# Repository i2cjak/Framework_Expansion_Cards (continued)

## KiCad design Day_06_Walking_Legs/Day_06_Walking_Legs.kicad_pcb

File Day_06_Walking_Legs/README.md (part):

# Day 06 — Walking Legs (Quadruped 2-DOF Expansion Card Set)

Four identical USB Type-C Expansion Cards plug flush into the four rear-set expansion bays (`Y = +36.0 mm` & `+76.6 mm`) of a Framework Laptop 13, anchoring a pair of reversible **12-gauge (`2.03 mm`) `5052-H32` aluminum Flank Stance-Extension Rails (`mech/leg_flank_bracket.step`)** that bolt across both bays per side and cantilever `93 mm` forward along/under the solid CNC aluminum bottom cover (`Y = -72.0 .. +94.0 mm`) to carry the front walking legs `81.0 mm` forward of the front ports (`Y = -45.0 mm` & `+67.0 mm`, `112.0 mm` balanced wheelbase) so the ~`1.3 kg` laptop stands walk-ready and executes static crawl and dynamic trot gaits.

---

## System Architecture & Engineering Calculations

### 1. Laptop Mass, Leg Kinematics & Torque Budget
- **Laptop + 4-Leg Mass:** $m_{\text{total}} \approx 1.30\text{ kg} + 4 \times 0.065\text{ kg} = 1.56\text{ kg}$ ($W = 15.3\text{ N}$).
- **Static & Dynamic Ground Reaction per Leg:**
  - Standing on 4 legs: $F_{z,\text{4-leg}} = 3.83\text{ N}$.
  - Static 3-leg crawl stance (worst-case CoM shift): $F_{z,\text{crawl}} \approx 6.2\text{ N}$.
  - Dynamic diagonal trot peak ($1.5\times$ impact factor across 2 diagonal legs): $F_{z,\text{trot}} \approx 11.5\text{ N}$.
- **Sagittal 2-DOF Linkage & Bellcrank Pushrod Geometry (`mech/`, `0 / 85` Full-ROM 3D Collisions Verified via `mech/simulate_walking_rom.py`):**
  - **Both MG90S metal-gear micro-servos** mount horizontally side-by-side (`X = ±9.00 mm, Z = +22.10 mm`) inside a high-arch MJF PA12 saddle (`mech/leg_servo_pod.step`, `17.6 mm` overhead crank headroom) with **both brass output splines pointing outboard (`-Y`)**, so all pivots act in the **`X–Z` sagittal walking plane** across 6 dedicated non-overlapping `Y` planes (`9.70 mm` tibia-to-rail clearance, `6.70 mm` pushrod-to-rail clearance, `3.17 mm` inboard-femur-to-pushrod clearance).
  - **Paired Upper Femur Links (`mech/leg_femur_link.step`, `qty: 8`):** $L_1 = 38.0\text{ mm}$ (`2.03 mm` `5052-H32` aluminum) driven directly by the Hip servo horn (`J2`) in symmetric double shear, supported outboard by `mech/leg_hip_bracket.step` (`ALU-063` overhead outrigger bridge) so radial ground loads bypass the servo shafts.
  - **Non-Crossing 4-Bar Knee Drive (`mech/leg_knee_pushrod.step`, `qty: 4` + `mech/leg_tibia_strut.step`, `qty: 4`):** The Knee servo (`J3`) drives a $12.0\text{ mm}$ crank arm coupled via a $36.0\text{ mm}$ `5052-H32` pushrod ($31.1^\circ\text{–}93.7^\circ$ transmission angle across the entire $48\times 26\text{ mm}$ foot workspace — zero dead-center singularity) to an integral $12.0\text{ mm}$ $90^\circ$ bellcrank lobe on the CNC-bent $61.5\text{ mm}$ ($L_2 = 47.0\text{ mm}$) sagittal U-channel tibia strut with an **open $15.0\text{ mm}$ upper clevis throat** (`Z = 39.5..61.5 mm`) so the twin femur links flex freely without front-web interference.
  - **Series-Elastic Compliant Arch Foot (`mech/leg_foot_pad.step`, `qty: 4`):** Printed in `95A` TPU (`22.5 mm` high-clearance ankle clevis tongue) with a through-arch oval suspension window flanked by twin elastomeric leaf-spring ribs ($\approx 3\text{ mm}$ progressive shock travel on foot strike) to cushion desk impacts and protect the servo gear trains.
  - Closed-loop 5-bar Jacobian virtual-work simulation (`m = 1.58 kg`):
    - 4-leg stand: $\tau_{\text{hip}} = 0.15\text{ N}\cdot\text{m}$ ($35\%$ of stall).
    - Static crawl peak joint torque: $\tau_{\text{crawl}} = \mathbf{0.30\text{ N}\cdot\text{m}}$ ($68\%$ of stall).
    - Paced diagonal trot ($0.85\text{ Hz}$): $\tau_{\text{trot}} = \mathbf{0.32\text{ N}\cdot\text{m}}$ ($73\%$ of the $\mathbf{0.44\text{ N}\cdot\text{m}}$ / $4.5\text{ kg}\cdot\text{cm}$ stall rating at $6.04\text{ V}$).

### 2. Framework Laptop 13 USB-C Port Power Validation (`2× 5 V @ 3.0 A` + `2× 5 V @ 1.5 A` = `45.0 W` PD Host Budget)
- **Host Port Specification:** With USB-PD wall power attached, two Framework Laptop 13 expansion bays source up to **`5.0 V @ 3.0 A` (`15.0 W` each = `30.0 W`)** and the other two bays source up to **`5.0 V @ 1.5 A` (`7.5 W` each = `15.0 W`)**, providing **`45.0 W` (`9.0 A @ 5.0 V`)** total across all four legs. Because two legs always land on **`1.5 A` (`7.5 W`)** bays, `1.50 A` on `5 V` `VBUS` is the binding per-leg design ceiling.
- **Simulated Per-Port & 4-Port `VBUS` Load (`mech/simulate_walking_rom.py`, `MT3608` `6.04 V` boost @ $\eta = 89\%$ + `32 mA` MCU/telemetry):**
  - **4-Leg Stand:** `0.57 A` avg / **`0.58 A` peak per port (`2.88 W`)** — `38.5%` of `1.5 A` port, `11.5 W` / `45.0 W` total.
  - **Belly Push-Up (`14 mm` stroke):** `0.48 A` avg / **`1.26 A` peak per port (`6.27 W`)** — `83.7%` of `1.5 A` port, `25.1 W` / `45.0 W` total.
  - **Static Crawl (`28 mm` stride):** `0.72 A` avg / **`1.22 A` peak per port (`6.08 W`)** — `81.0%` of `1.5 A` port, `16.3 W` / `45.0 W` total.
  - **Paced Diagonal Trot (`0.85 Hz`):** `0.67 A` avg / **`1.51 A` raw impact peak** (`17.7 W` / `45.0 W` 4-port total) — supplied locally during `~20 ms` foot-strike peaks by the `88 µF` (`+6V0_SERVO`) ceramic reservoir and capped below `1.50 A` at **`1.38 A`** on `1.5 A` ports.
  - **Sprint Trot (`1.05 Hz`) / Dual-Servo Hard Stall (`2.53 A` raw):** `3.0 A` (`15 W`) ports carry full dual-servo stall continuously (`84%`), whereas `1.5 A` (`7.5 W`) ports are protected by **`0.14 ms` hardware overcurrent foldback** (`INA226` `140 µs` `SOL` alert at **`1.38 A` / `27.6 mV`** across `R8` wired to `PB12` `EXTI12` ISR — $>30\times$ faster than the motherboard port switch OCP!).
- **Pulsed `12 ms` Precharge Soft-Start (`0.22 A` Peak vs `32.4 A` Hard Step):**
  1. Snapping `Q1` (`AO3401A`) hard ON into `110 µF` total capacitance (`C12 = 22 µF` + `4× 22 µF = 88 µF` boost reservoir through `L1`/`D4`) would draw a `32.4 A` microsecond spike and trip a `1.5 A` port switch.
  2. `firmware/main.c` (`set_servo_power`) staggers each bay by `bay_id × 40 ms` and pulses `PB4` at `25 kHz` (`1 → 8 µs` duty over `12 ms`) while `BOOST_EN = LOW`, using `L1`'s `di/dt` limit to precharge the `110 µF` bank to `4.70 V` at **`0.22 A` peak port current** before latching `Q1` ON and enabling `U5` (`MT3608` `6.04 V`).

### 3. Sub-Microsecond Multi-Card Gait Coordination (`1 kHz` USB `SOF`)
- All four Expansion Cards enumerate on the laptop's internal xHCI root hub, which broadcasts the USB Full-Speed **Start-Of-Frame (`SOF`)** packet every `1.000 ms` with `< 500 ns` skew across all four ports.
- `software/walk_controller.py` streams trajectory packets tagged with a target 11-bit `SOF` frame number `(FNR + 5) & 0x7FF`.
- On each card, `USB_LP_CAN1_RX0_IRQHandler` phase-locks `TIM2`'s `200 Hz` (`5000 µs`, `1 µs` resolution) hardware PWM counter to `FNR % 5 == 0` and commits `HIP_PWM` (`PA0`) and `KNEE_PWM` (`PA1`) simultaneously on the target `SOF` edge—achieving deterministic 4-leg synchronization with zero external sync wires.

### 4. Rear-Set Port Geometry, Reversible `ALU-080` Flank Stance-Extension Rail & SendCutSend DFM
- **Why Direct Port Mounting Fails Fore-Aft Balance (`FW_MAIN_PCB_GENERIC_2` Port Coordinates):** On a Framework Laptop 13 (`228.9 mm` front-to-back, `Y = -114.45 .. +114.45 mm`), **both** physical Expansion Card bays on each flank sit in the **rear half** of the laptop (`Y = +36.0 mm` Front Port and `Y = +76.6 mm` Rear Port, `40.60 mm` center-to-center pitch with a `10.6 mm` aluminum divider), while the entire front `135.45 mm` (`Y = -114.45 .. +21.0 mm`, battery + palmrest) has zero expansion bays. Mounting legs directly at the ports would leave `150 mm` of unsupported front laptop mass ahead of the front legs.
- **Reversible Flank Stance-Extension Rail (`mech/leg_flank_bracket.step`, `ALU-080` `2.03 mm` `12-gauge` `5052-H32`, `qty: 2`):** Each `166.0 × 49.0 × 12.5 mm` CNC-bent inverted U-channel rail (`Y = -24.5 .. +24.5 mm`, giving `9.70 mm` outboard clearance to the `leg_tibia_strut` U-channel and `6.70 mm` clearance to `leg_knee_pushrod`) bolts across **both** rear-set `leg_bay_housing` plugs on a flank (`8× M2.5` across the `40.6 mm` two-bay baseline, locking out yaw twist) and extends **`93 mm` forward** along the laptop flank and `24.5 mm` underneath the solid CNC aluminum bottom cover (`Y = -72.0 .. +94.0 mm`, clearing both the `|X| = 111.5 mm` card-release latch buttons and the `Y = ±103 mm` rubber foot strips). It carries the **Front `leg_servo_pod` at `Y = -45.0 mm`** (`81.0 mm` forward of the Front Port — reacting front-leg vertical loads straight upward into the solid aluminum bottom cover right above `Y = -45.0 mm` with zero port prying!) and the **Rear `leg_servo_pod` at `Y = +67.0 mm`** (`112.0 mm` balanced quadruped wheelbase). A mirror-symmetric 24-hole layout lets **one single reversible SKU (`qty: 2`)** fit both Left and Right flanks (`37 pass · 0 fail · 0 warn` SendCutSend live DFM).
- **Modular Printed Plugs & Saddles (`MJF PA12 Nylon`):**
  - `mech/leg_bay_housing.step` (`qty: 4`) — Open-top `30 × 32 × 6.8 mm` Expansion Card bay cartridge housing the double-sided `5.44 mm` Z-span `Day_06` PCB (`SM03B-SRSS-TB(LF)(SN)` `1.0 mm` JST-SH side-entry servo headers `J2`/`J3`, `MWSA0518S-4R7MT` `1.8 mm` shielded inductor `L1`, and `SS34FA` `SOD-123F` Schottky `D4` — verified `0.000 mm³` interference across all 86 3D component solids) at `Y = +36.0` & `+76.6 mm`, with straight-in front mating for dual 3-wire `#28 AWG` silicone servo harnesses (`4× M2.5 × 2.5 mm` floor heat-set inserts).
  - `mech/leg_servo_pod.step` (`qty: 4`) — Modular outboard dual-`MG90S` saddle (`27.50 mm` exact servo ear pitch) bolted at `Y = -45.0` & `+67.0 mm` on the outboard deck of `leg_flank_bracket` (`4× M2.5 × 3.0 mm` floor heat-set inserts + `4× M2.5 × 3.0 mm` roof heat-set inserts for `leg_hip_bracket`).
- **SendCutSend `5052-H32` Aluminum Sheet-Metal Set (`0 fail · 0 warn` live DFM verified across all 5 sheet-metal parts):**
  - `mech/leg_flank_bracket.flat.dxf` (`ALU-080` `2.03 mm` CNC-bent `166.0 mm` reversible flank stance-extension U-channel rail, `qty: 2` — `37 pass · 0 fail · 0 warn`).
  - `mech/leg_hip_bracket.flat.dxf` (`ALU-063` `1.60 mm` CNC-bent 90° overhead double-shear bearing outrigger, `qty: 4` — `25 pass · 0 fail · 0 warn`).
  - `mech/leg_femur_link.dxf` (`ALU-080` `2.03 mm` laser-cut `38.0 mm` sagittal femur link, `qty: 8` — `13 pass · 0 fail · 0 warn`).
  - `mech/leg_knee_pushrod.dxf` (`ALU-080` `2.03 mm` laser-cut `36.0 mm` knee actuation pushrod, `qty: 4` — `13 pass · 0 fail · 0 warn`).
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
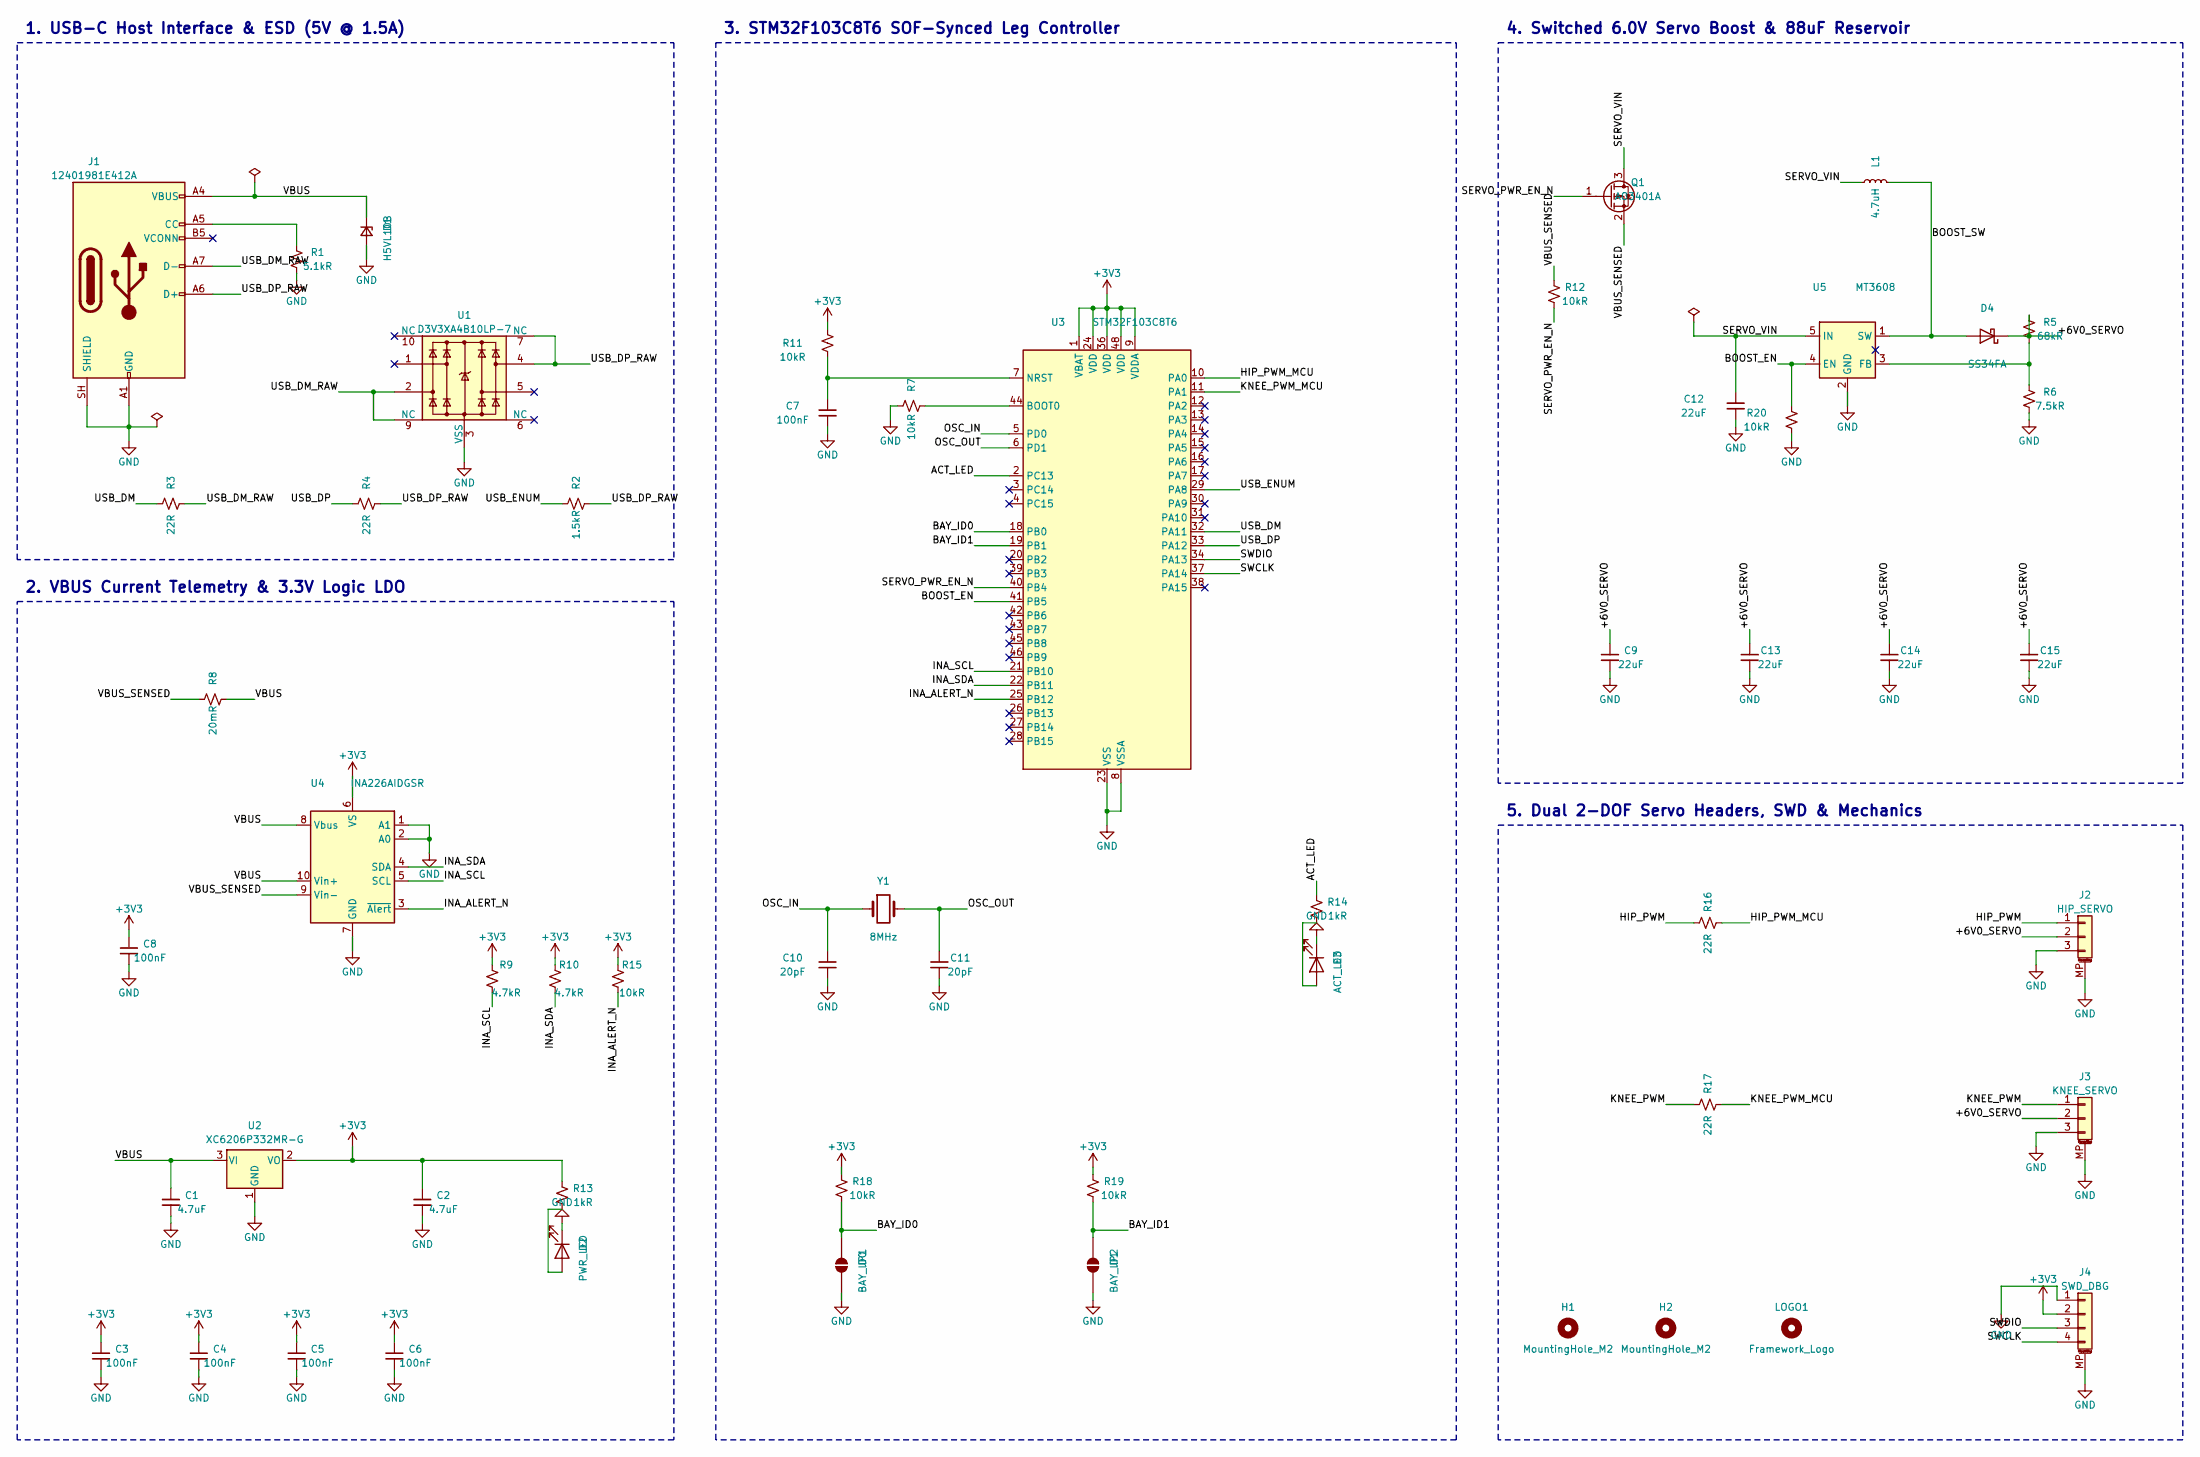
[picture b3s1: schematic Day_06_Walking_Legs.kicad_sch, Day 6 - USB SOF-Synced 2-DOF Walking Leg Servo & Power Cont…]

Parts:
C1, C2: 4.7uF; C_0603_1608Metric; MPN CL10A475KO8NNNC; LCSC C19666
C3, C4, C5, C6, C7, C8: 100nF; C_0402_1005Metric; MPN CL05B104KB54PNC; LCSC C307331
C9, C12, C13, C14, C15: 22uF; C_1206_3216Metric; MPN CL31A226KAHNNNE; LCSC C12891
C10, C11: 20pF; C_0402_1005Metric; MPN 0402CG200J500NT; LCSC C1554
D1: H5VL10B; D_SOD-882; MPN H5VL10B; LCSC C7420372
D2: PWR_LED; LED_0603_1608Metric; MPN KT-0603W; LCSC C2290
D3: ACT_LED; LED_0603_1608Metric; MPN KT-0603R; LCSC C2286
D4: SS34FA; D_SOD-123F; MPN SS34FA; LCSC C719833
H1, H2: MountingHole_M2; MountingHole_2.2mm_M2
J1: 12401981E412A; USB_C_Plug_Amphenol_12401981E412A; MPN 12401981E412A; LCSC C5428559
J2: HIP_SERVO; JST_SH_SM03B-SRSS-TB_1x03-1MP_P1.00mm_Horizontal; MPN SM03B-SRSS-TB(LF)(SN); LCSC C160403
J3: KNEE_SERVO; JST_SH_SM03B-SRSS-TB_1x03-1MP_P1.00mm_Horizontal; MPN SM03B-SRSS-TB(LF)(SN); LCSC C160403
J4: SWD_DBG; JST_SH_SM04B-SRSS-TB_1x04-1MP_P1.00mm_Horizontal; MPN SM04B-SRSS-TB(LF)(SN); LCSC C160404
JP1: BAY_ID0; SolderJumper-2_P1.3mm_Open_RoundedPad1.0x1.5mm
JP2: BAY_ID1; SolderJumper-2_P1.3mm_Open_RoundedPad1.0x1.5mm
L1: 4.7uH; L_Sunlord_MWSA0518S; MPN MWSA0518S-4R7MT; LCSC C408347
LOGO1: Framework_Logo; Framework-Logo_1.5mm_SilkScreen
Q1: AO3401A; SOT-23; MPN AO3401A; LCSC C15127
R1: 5.1kR; R_0402_1005Metric; MPN 0402WGF5101TCE; LCSC C25905
R2: 1.5kR; R_0402_1005Metric; MPN 0402WGF1501TCE; LCSC C25867
R3, R4, R16, R17: 22R; R_0402_1005Metric; MPN 0402WGF220JTCE; LCSC C25092
R5: 68kR; R_0402_1005Metric; MPN 0402WGF6802TCE; LCSC C36871
R6: 7.5kR; R_0402_1005Metric; MPN 0402WGF7501TCE; LCSC C25918
R7, R11, R12, R15, R18, R19, R20: 10kR; R_0402_1005Metric; MPN 0402WGF1002TCE; LCSC C25744
R8: 20mR; R_1206_3216Metric; MPN 1206W3F200MT5E; LCSC C2765435
R9, R10: 4.7kR; R_0402_1005Metric; MPN 0402WGF4701TCE; LCSC C25900
R13, R14: 1kR; R_0402_1005Metric; MPN 0402WGF1001TCE; LCSC C11702
U1: D3V3XA4B10LP-7; Diodes_UDFN-10_1x2.5mm_P0.5mm; MPN D3V3XA4B10LP-7; LCSC C1980462
U2: XC6206P332MR-G; SOT-23; MPN XC6206P332MR-G; LCSC C5446
U3: STM32F103C8T6; LQFP-48_7x7mm_P0.5mm; MPN STM32F103C8T6; LCSC C8734
U4: INA226AIDGSR; MSOP-10_3x3mm_P0.5mm; MPN INA226AIDGSR; LCSC C49851
U5: MT3608; SOT-23-6; MPN MT3608; LCSC C84817
Y1: 8MHz; Crystal_SMD_5032-2Pin_5.0x3.2mm; MPN X50328MSB2GI; LCSC C115962

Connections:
+3V3: C2.1, C3.1, C4.1, C5.1, C6.1, C8.1, J4.2, R9.1, R10.1, R11.1, R13.1, R15.1, R18.1, R19.1, U2.2 (VO), U3.1 (VBAT), U3.9 (VDDA), U3.24 (VDD), U3.36 (VDD), U3.48 (VDD), U4.6 (VS)
/+6V0_SERVO: C9.1, C13.1, C14.1, C15.1, D4.1 (K), J2.2, J3.2, R5.1
/ACT_LED: R14.1, U3.2 (PC13)
/BAY_ID0: JP1.2 (B), R18.2, U3.18 (PB0)
/BAY_ID1: JP2.2 (B), R19.2, U3.19 (PB1)
/BOOST_EN: R20.1, U3.41 (PB5), U5.4 (EN)
/BOOST_SW: D4.2 (A), L1.2, U5.1 (SW)
/HIP_PWM: J2.1, R16.1
/HIP_PWM_MCU: R16.2, U3.10 (PA0)
/INA_ALERT_N: R15.2, U3.25 (PB12), U4.3 (~Alert)
/INA_SCL: R9.2, U3.21 (PB10), U4.5 (SCL)
/INA_SDA: R10.2, U3.22 (PB11), U4.4 (SDA)
/KNEE_PWM: J3.1, R17.1
/KNEE_PWM_MCU: R17.2, U3.11 (PA1)
/OSC_IN: C10.1, U3.5 (PD0), Y1.1
/OSC_OUT: C11.1, U3.6 (PD1), Y1.2
/SERVO_PWR_EN_N: Q1.1 (G), R12.2, U3.40 (PB4)
/SERVO_VIN: C12.1, L1.1, Q1.3 (D), U5.5 (IN)
/SWCLK: J4.4, U3.37 (PA14)
/SWDIO: J4.3, U3.34 (PA13)
/USB_DM: R3.1, U3.32 (PA11)
/USB_DM_RAW: J1.A7 (D-), R3.2, U1.2, U1.9 (NC)
/USB_DP: R4.1, U3.33 (PA12)
/USB_DP_RAW: J1.A6 (D+), R2.2, R4.2, U1.4, U1.7 (NC)
/USB_ENUM: R2.1, U3.29 (PA8)
/VBUS: C1.1, D1.1 (K), J1.A4 (VBUS), J1.A9 (VBUS), J1.B4 (VBUS), J1.B9 (VBUS), R8.2, U2.3 (VI), U4.8 (Vbus), U4.10 (Vin+)
/VBUS_SENSED: Q1.2 (S), R8.1, R12.1, U4.9 (Vin-)
GND: C1.2, C2.2, C3.2, C4.2, C5.2, C6.2, C7.2, C8.2, C9.2, C10.2, C11.2, C12.2, C13.2, C14.2, C15.2, D1.2 (A), D2.1 (K), D3.1 (K), J1.A1 (GND), J1.A12 (GND), J1.B1 (GND), J1.B12 (GND), J1.SH (SHIELD), J2.3, J2.MP (MountPin), J3.3, J3.MP (MountPin), J4.1, J4.MP (MountPin), JP1.1 (A), JP2.1 (A), R1.2, R6.2, R7.1, R20.2, U1.3 (VSS), U1.8 (VSS), U2.1 (GND), U3.8 (VSSA), U3.23 (VSS), U3.35 (VSS), U3.47 (VSS), U4.1 (A1), U4.2 (A0), U4.7 (GND), U5.2 (GND)
unnamed: D2.2 (A), R13.2
unnamed: D3.2 (A), R14.2
unnamed: J1.A5 (CC), R1.1
unnamed: R7.2, U3.44 (BOOT0)
unnamed: C7.1, R11.2, U3.7 (NRST)
unnamed: R5.2, R6.1, U5.3 (FB)

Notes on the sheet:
1. USB-C Host Interface & ESD (5V @ 1.5A)
2. VBUS Current Telemetry & 3.3V Logic LDO
3. STM32F103C8T6 SOF-Synced Leg Controller
4. Switched 6.0V Servo Boost & 88uF Reservoir
5. Dual 2-DOF Servo Headers, SWD & Mechanics

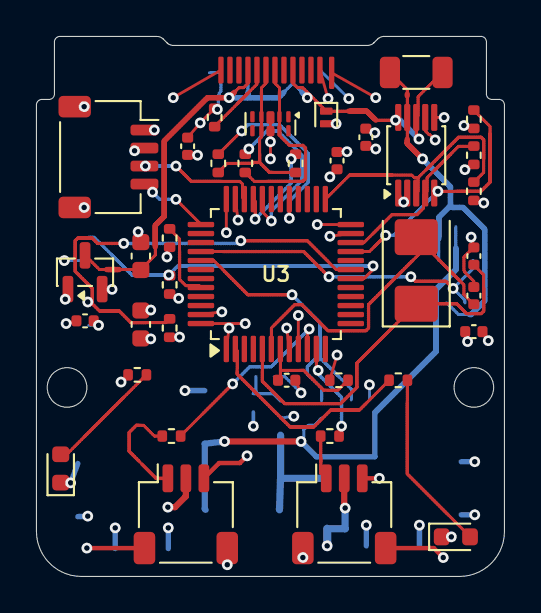
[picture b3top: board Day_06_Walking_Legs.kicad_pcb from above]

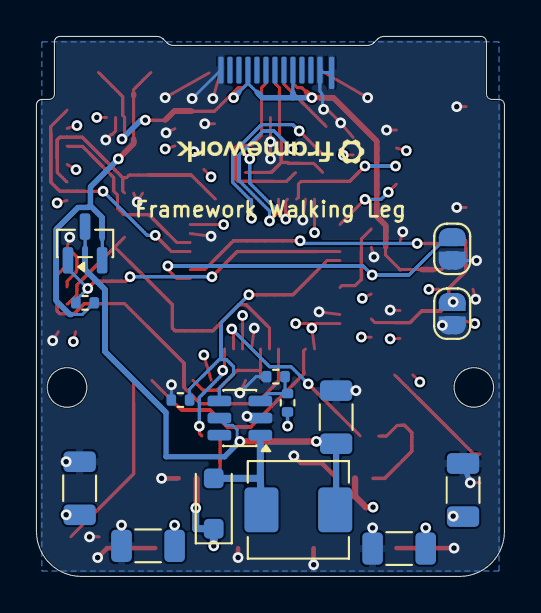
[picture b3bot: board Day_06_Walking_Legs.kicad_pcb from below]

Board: 4 copper layers, 26.0 x 30.0 mm, 56 parts (16 on the bottom side), 34 nets.

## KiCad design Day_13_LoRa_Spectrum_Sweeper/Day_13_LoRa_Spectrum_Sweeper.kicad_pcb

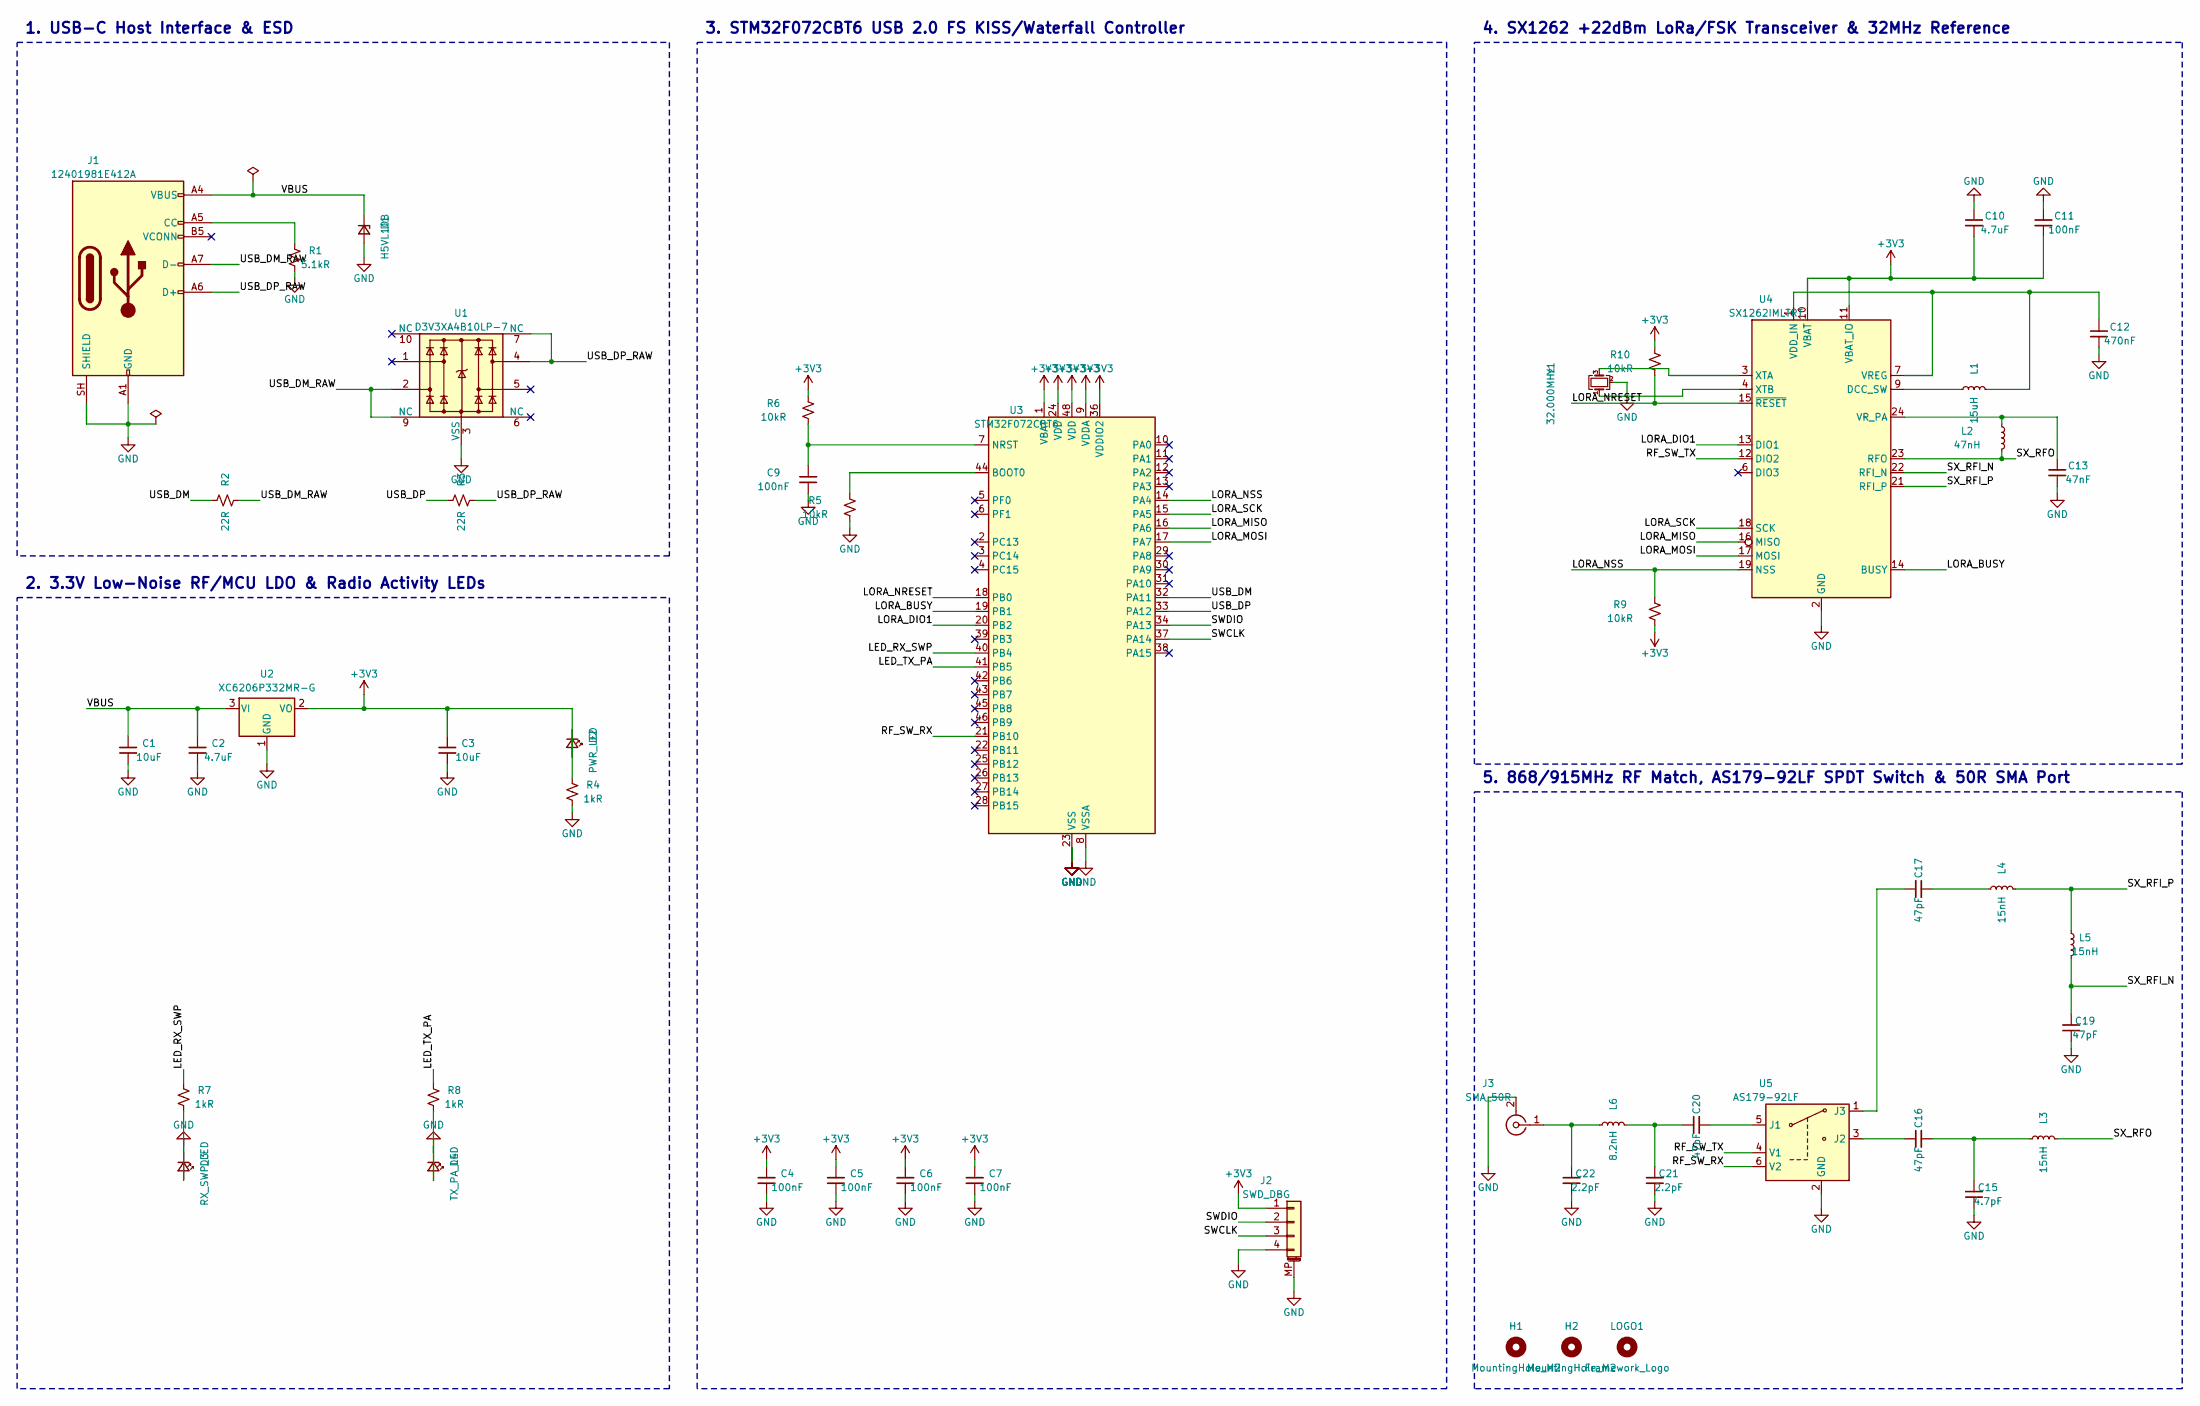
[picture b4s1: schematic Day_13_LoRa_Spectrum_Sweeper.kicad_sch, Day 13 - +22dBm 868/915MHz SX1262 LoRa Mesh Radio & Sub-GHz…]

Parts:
C1, C3: 10uF; C_0805_2012Metric; MPN CL21A106KAYNNNE; LCSC C15850
C2, C10: 4.7uF; C_0603_1608Metric; MPN CL10A475KO8NNNC; LCSC C19666
C4, C5, C6, C7, C9, C11: 100nF; C_0402_1005Metric; MPN CL05B104KB54PNC; LCSC C307331
C12: 470nF; C_0402_1005Metric; MPN CL05A474KP5NNNC; LCSC C47339
C13: 47nF; C_0402_1005Metric; MPN TCC0402X7R473K500AT; LCSC C880605
C15: 4.7pF; C_0402_1005Metric; MPN 0402CG4R7C500NT; LCSC C1569
C16, C17, C19, C20: 47pF; C_0402_1005Metric; MPN 0402CG470J500NT; LCSC C1567
C21, C22: 2.2pF; C_0402_1005Metric; MPN 0402CG2R2C500NT; LCSC C1559
D1: H5VL10B; D_SOD-882; MPN H5VL10B; LCSC C7420372
D2: PWR_LED; LED_0603_1608Metric; MPN 19-217/GHC-YR1S2/3T; LCSC C2290
D3: RX_SWP_LED; LED_0603_1608Metric; MPN 19-217/GHC-YR1S2/3T; LCSC C2290
D4: TX_PA_LED; LED_0603_1608Metric; MPN KT-0603R; LCSC C2286
H1, H2: MountingHole_M2; MountingHole_2.2mm_M2
J1: 12401981E412A; USB_C_Plug_Amphenol_12401981E412A; MPN 12401981E412A; LCSC C5428559
J2: SWD_DBG; JST_SH_SM04B-SRSS-TB_1x04-1MP_P1.00mm_Horizontal; MPN SM04B-SRSS-TB(LF)(SN); LCSC C160404
J3: SMA_50R; SMA_Samtec_SMA-J-P-H-ST-EM1_EdgeMount; MPN BWSMA-KE-Z001; LCSC C496549
L1: 15uH; L_0603_1608Metric; MPN MGFL1608F150MT-LF; LCSC C486329
L2: 47nH; L_0402_1005Metric; MPN VHF100505HQ47NJT; LCSC C395068
L3, L4, L5: 15nH; L_0402_1005Metric; MPN SDCL1005C15NJTDF; LCSC C27143
L6: 8.2nH; L_0402_1005Metric; MPN LQG15HS8N2J02D; LCSC C98003
LOGO1: Framework_Logo; Framework-Logo_1.5mm_SilkScreen
R1: 5.1kR; R_0402_1005Metric; MPN 0402WGF5101TCE; LCSC C25905
R2, R3: 22R; R_0402_1005Metric; MPN 0402WGF220JTCE; LCSC C25092
R4, R7, R8: 1kR; R_0402_1005Metric; MPN 0402WGF1001TCE; LCSC C11702
R5, R6, R9, R10: 10kR; R_0402_1005Metric; MPN 0402WGF1002TCE; LCSC C25744
U1: D3V3XA4B10LP-7; Diodes_UDFN-10_1x2.5mm_P0.5mm; MPN D3V3XA4B10LP-7; LCSC C1980462
U2: XC6206P332MR-G; SOT-23; MPN XC6206P332MR-G; LCSC C5446
U3: STM32F072CBT6; LQFP-48_7x7mm_P0.5mm; MPN STM32F072CBT6; LCSC C81720
U4: SX1262IMLTRT; QFN-24-1EP_4x4mm_P0.5mm_EP2.5x2.5mm; MPN SX1262IMLTRT; LCSC C191341
U5: AS179-92LF; SOT-363_SC-70-6; MPN AS179-92LF; LCSC C83422
Y1: 32.000MHz; Crystal_SMD_3225-4Pin_3.2x2.5mm; MPN X322532MOB4SI; LCSC C9009

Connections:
+3V3: C3.1, C4.1, C5.1, C6.1, C7.1, C10.2, C11.2, D2.2 (A), J2.1, R6.1, R9.2, R10.1, U2.2 (VO), U3.1 (VBAT), U3.9 (VDDA), U3.24 (VDD), U3.36 (VDDIO2), U3.48 (VDD), U4.10 (VBAT), U4.11 (VBAT_IO)
/LED_RX_SWP: R7.1, U3.40 (PB4)
/LED_TX_PA: R8.1, U3.41 (PB5)
/LORA_BUSY: U3.19 (PB1), U4.14 (BUSY)
/LORA_DIO1: U3.20 (PB2), U4.13 (DIO1)
/LORA_MISO: U3.16 (PA6), U4.16 (MISO)
/LORA_MOSI: U3.17 (PA7), U4.17 (MOSI)
/LORA_NRESET: R10.2, U3.18 (PB0), U4.15 (~RESET)
/LORA_NSS: R9.1, U3.14 (PA4), U4.19 (NSS)
/LORA_SCK: U3.15 (PA5), U4.18 (SCK)
/RF_SW_RX: U3.21 (PB10), U5.6 (V2)
/RF_SW_TX: U4.12 (DIO2), U5.4 (V1)
/SWCLK: J2.3, U3.37 (PA14)
/SWDIO: J2.2, U3.34 (PA13)
/SX_RFI_N: C19.1, L5.2, U4.22 (RFI_N)
/SX_RFI_P: L4.2, L5.1, U4.21 (RFI_P)
/SX_RFO: L2.2, L3.2, U4.23 (RFO)
/USB_DM: R2.1, U3.32 (PA11)
/USB_DM_RAW: J1.A7 (D-), R2.2, U1.2, U1.9 (NC)
/USB_DP: R3.1, U3.33 (PA12)
/USB_DP_RAW: J1.A6 (D+), R3.2, U1.4, U1.7 (NC)
/VBUS: C1.1, C2.1, D1.1 (K), J1.A4 (VBUS), J1.A9 (VBUS), J1.B4 (VBUS), J1.B9 (VBUS), U2.3 (VI)
unnamed: C15.1, C16.2, L3.1
unnamed: C17.2, L4.1
unnamed: C20.1, C21.1, L6.2
unnamed: D2.1 (K), R4.1
unnamed: J1.A5 (CC), R1.1
unnamed: C22.1, J3.1 (In), L6.1
unnamed: R5.1, U3.44 (BOOT0)
unnamed: C9.1, R6.2, U3.7 (NRST)
unnamed: L1.1, U4.9 (DCC_SW)
unnamed: C12.1, L1.2, U4.1 (VDD_IN), U4.7 (VREG)
unnamed: C13.1, L2.1, U4.24 (VR_PA)
unnamed: U4.3 (XTA), Y1.3
unnamed: C20.2, U5.5 (J1)
unnamed: C16.1, U5.3 (J2)
unnamed: C17.1, U5.1 (J3)

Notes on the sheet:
1. USB-C Host Interface & ESD
2. 3.3V Low-Noise RF/MCU LDO & Radio Activity LEDs
3. STM32F072CBT6 USB 2.0 FS KISS/Waterfall Controller
4. SX1262 +22dBm LoRa/FSK Transceiver & 32MHz Reference
5. 868/915MHz RF Match, AS179-92LF SPDT Switch & 50R SMA Port

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
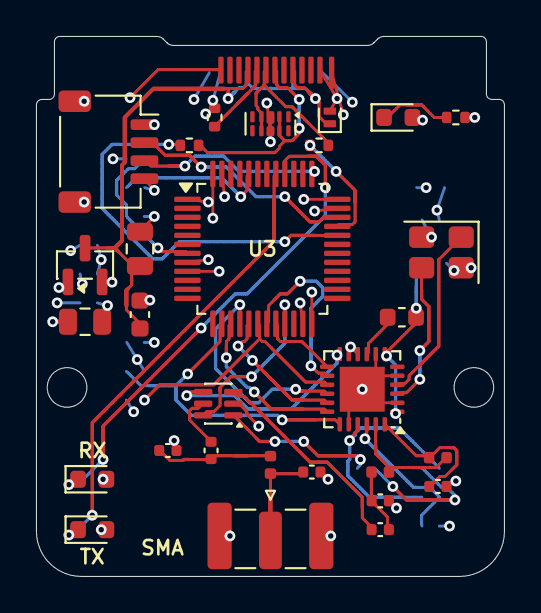
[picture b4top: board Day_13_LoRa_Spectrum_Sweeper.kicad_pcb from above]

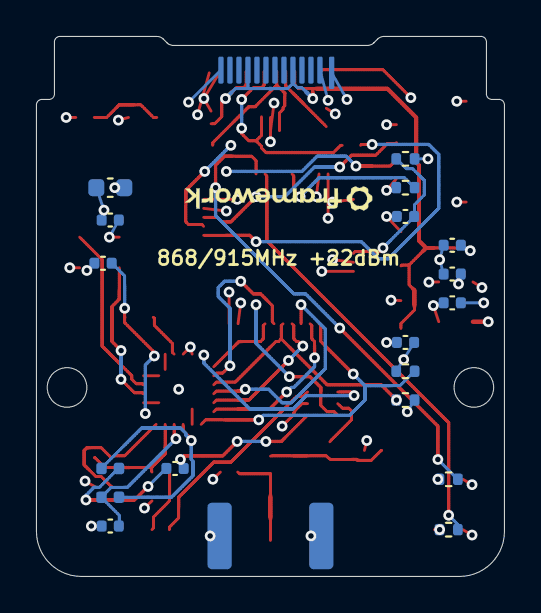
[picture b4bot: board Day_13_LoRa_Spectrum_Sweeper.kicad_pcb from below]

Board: 4 copper layers, 26.0 x 30.0 mm, 51 parts (19 on the bottom side), 41 nets.

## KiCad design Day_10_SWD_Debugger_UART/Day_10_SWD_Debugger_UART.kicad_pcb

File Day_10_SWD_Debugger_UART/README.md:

# Day 10 — Autoleveling `1.65V–5.5V` CMSIS-DAPv2 SWD Debugger & Target UART Bridge

A flush-fit ARM Cortex-M / RISC-V `CMSIS-DAPv2` hardware debug probe and `6 Mbps` target `UART` / `SWO` bridge inside a `26.0 × 30.0 mm` Framework Laptop Expansion Card, featuring true `1.65 V – 5.5 V` dual-supply level translation across every target signal.

## Hardware Architecture

1. **Five-Channel `420 Mbps` `1.65V–5.5V` Autoleveling Front-End (`U4`–`U8` — `5×` TI `SN74LVC1T45DBVR`):**
   - Each signal uses an independent dual-supply (`VCCA = +3.3 V`, `VCCB = VTREF`) `SOT-23-6` bus transceiver with `I_off` partial-power-down isolation: when a target board is powered off (`VTREF = 0 V`), all target pins remain high-impedance (`Hi-Z`) with zero back-powering.
   - **`U4` (`SWDIO`):** Hardware direction-controlled turnaround (`PB12` with `10 kΩ` reset pull-down `R17` so `U4` powers up in passive `B → A` input mode).
   - **`U5` (`SWCLK`):** Dedicated low-skew `SPI2_SCK` / GPIO clock translator (`PB13`).
   - **`U6` (`nRESET` Bidirectional Open-Drain + Target Reset Sense):** `PB0` controls `DIR` (`10 kΩ` pull-down `R18` defaults `U6` to `B → A` `Hi-Z` release at boot so `PB1` monitors external target reset button presses without contention; asserting `PB1 = 0` + `PB0 = 1` actively sinks target `nRESET` to `0.0 V` at `1.65 V – 5.5 V`).
   - **`U7` & `U8` (`UART TX` & `UART RX / SWO`):** Independent `USART2` DMA transmit/receive channels (`PA2`/`PA3`) with `22 Ω` series damping resistors (`R12`–`R16`) and weak `100 kΩ` RX idle pull-up (`R19`).

2. **`VTref` Surge Protection & Millivolt ADC Telemetry (`D3`, `R5`–`R7`, `C7`, `C8`):**
   - `H5VL10B` bidirectional TVS (`D3`), `22 Ω` surge limiter (`R5`), and `4.7 µF` + `5× 100 nF` decoupling condition the sensed target supply rail, while a `2:1` (`100 kΩ / 100 kΩ`) precision divider reports `0.00 V – 6.60 V` `VTref` to `PA0` (`ADC_IN0`) for `CMSIS-DAPv2` `DAP_Info` target-power verification.

3. **Crystal-Less USB 2.0 FS Controller & Dual Shrouded `1.0 mm` Bezel Ports (`U3`, `J2`, `J3`):**
   - `STM32F072CBT6` (`U3`, `48 MHz` `HSI48` + `CRS` `SOF` clock recovery) exposes `WinUSB` `CMSIS-DAPv2` bulk endpoints (zero-driver plug-and-play in `OpenOCD`, `pyOCD`, `probe-rs`, and `VS Code Cortex-Debug`) alongside a standard `CDC-ACM` Virtual COM Port.
   - Two side-by-side shrouded `4`-pin `1.0 mm` JST-SH connectors on the outward bezel separate `TGT_SWD` (`J2`: `VTref`, `SWDIO`, `SWCLK`, `GND`) and `TGT_UART` (`J3`: `nRESET`, `TGT_TX`, `TGT_RX`, `GND`) alongside `DAP` and `UART` activity LEDs (`D4`, `D5`).

## Fabrication & Build

All components are sourced from the fab's stock on a `0.8 mm` 4-layer ENIG stackup (`Day_10_SWD_Debugger_UART.fab.json`). Regenerate ERC/DRC reports, Gerbers, placement files, STEP model, and 3D renders with:

```bash
python3 build.py
```

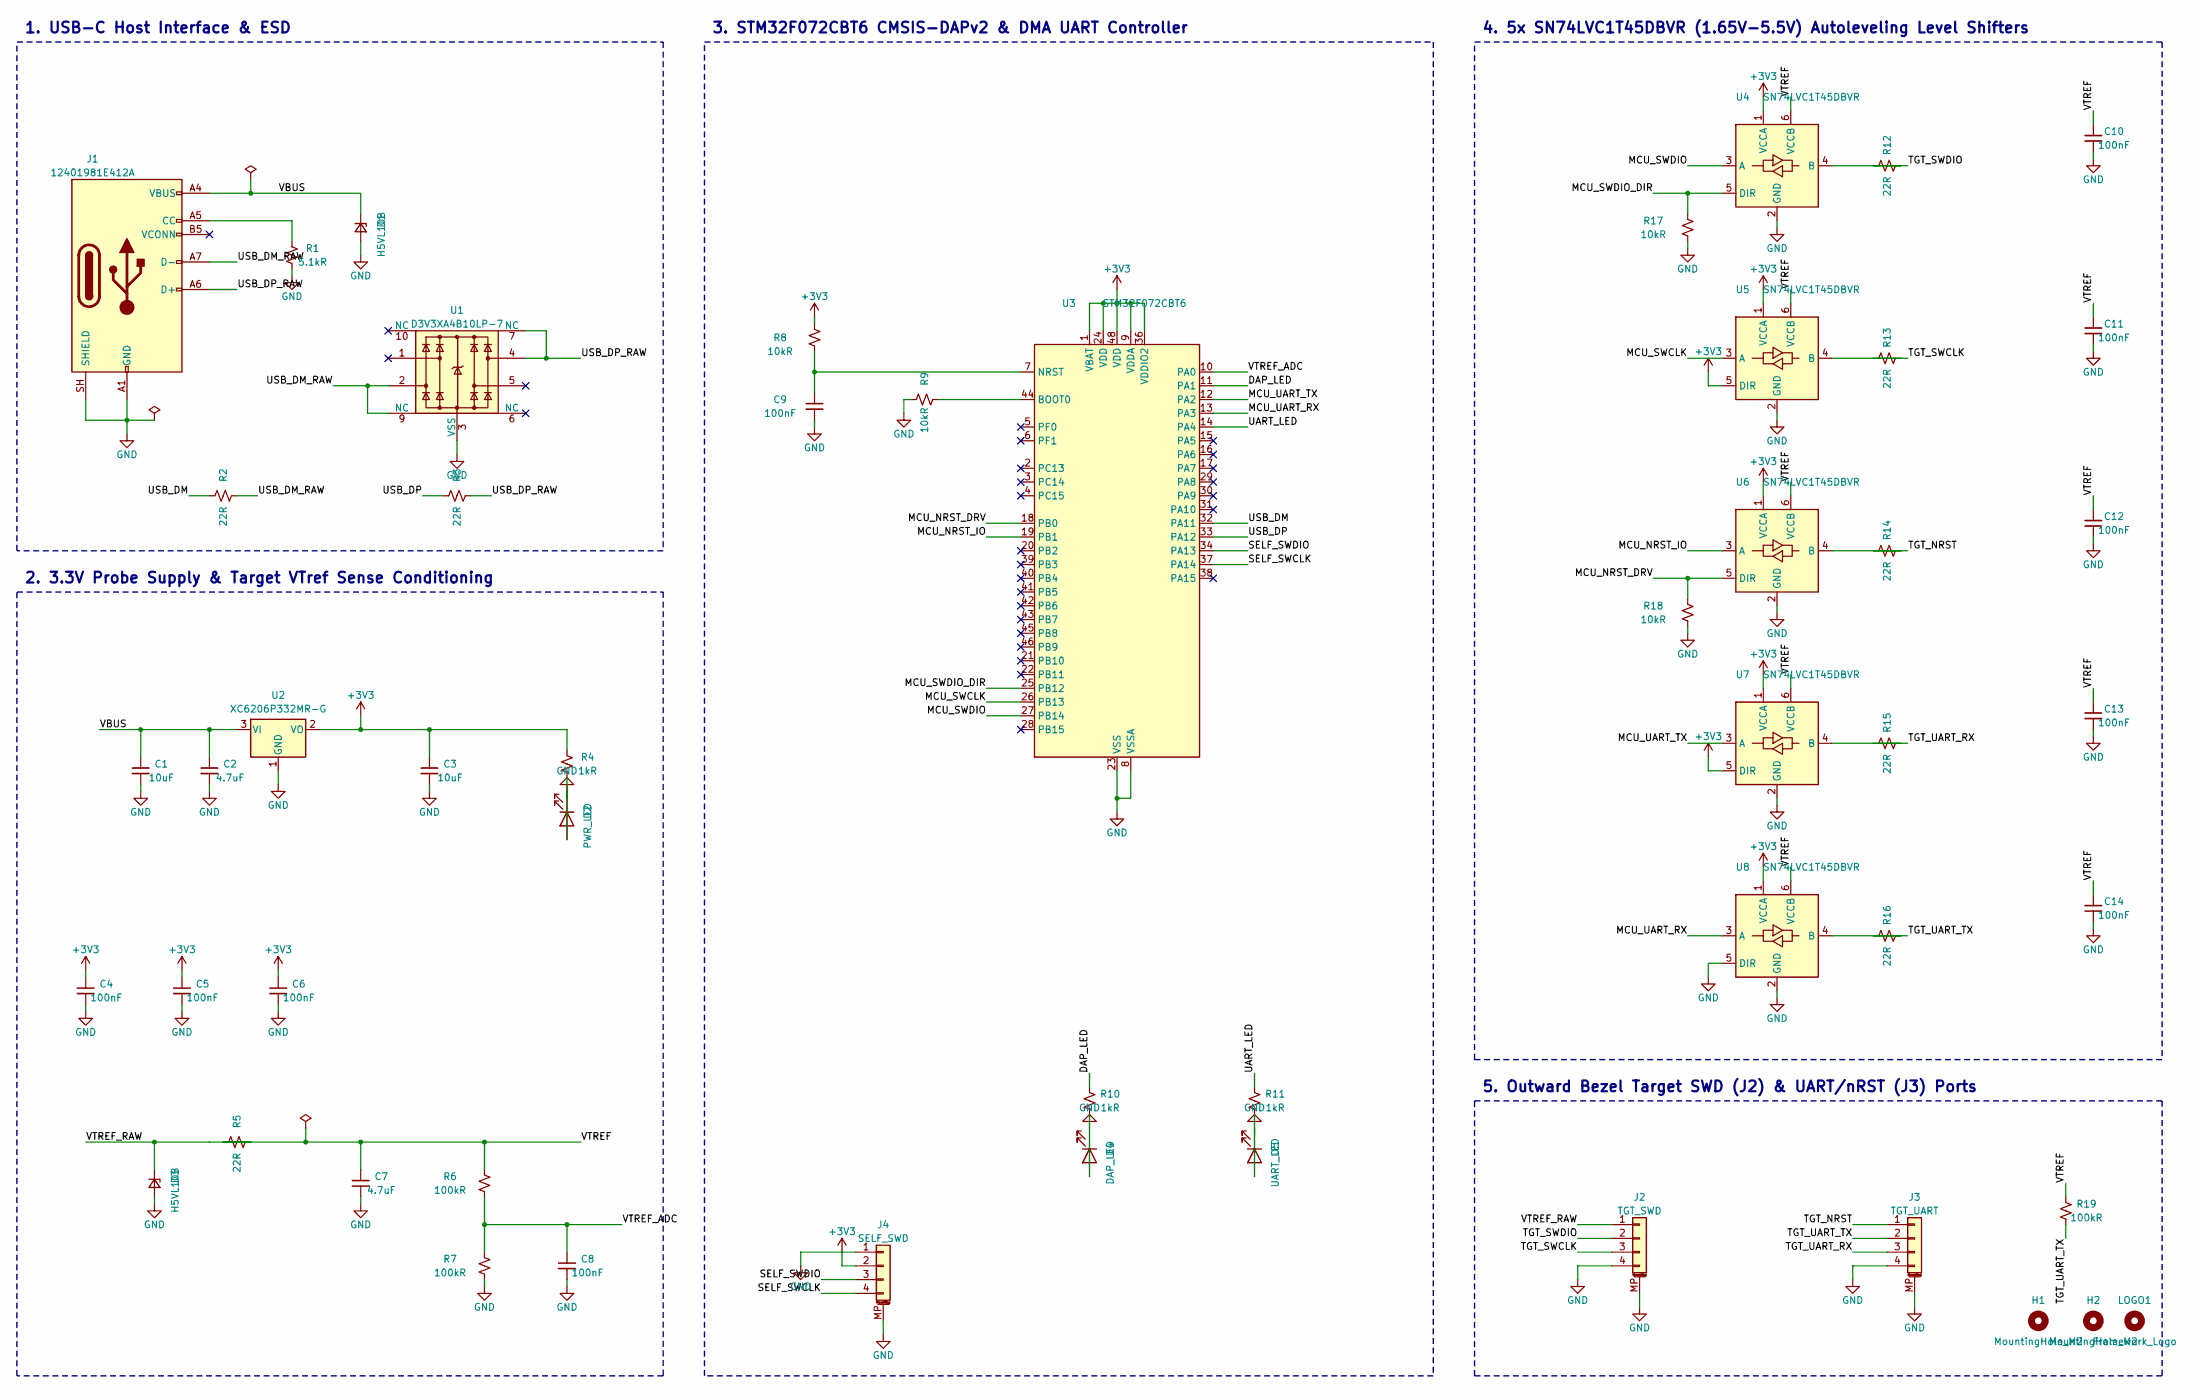
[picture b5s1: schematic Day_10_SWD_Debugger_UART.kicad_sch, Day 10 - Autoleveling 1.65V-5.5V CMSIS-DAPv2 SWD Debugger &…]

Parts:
C1, C3: 10uF; C_0805_2012Metric; MPN CL21A106KAYNNNE; LCSC C15850
C2, C7: 4.7uF; C_0603_1608Metric; MPN CL10A475KO8NNNC; LCSC C19666
C4, C5, C6, C8, C9, C10, C11, C12, C13, C14: 100nF; C_0402_1005Metric; MPN CL05B104KB54PNC; LCSC C307331
D1, D3: H5VL10B; D_SOD-882; MPN H5VL10B; LCSC C7420372
D2: PWR_LED; LED_0603_1608Metric; MPN KT-0603G; LCSC C2297
D4: DAP_LED; LED_0603_1608Metric; MPN KT-0603W; LCSC C2290
D5: UART_LED; LED_0603_1608Metric; MPN KT-0603R; LCSC C2286
H1, H2: MountingHole_M2; MountingHole_2.2mm_M2
J1: 12401981E412A; USB_C_Plug_Amphenol_12401981E412A; MPN 12401981E412A; LCSC C5428559
J2: TGT_SWD; JST_SH_SM04B-SRSS-TB_1x04-1MP_P1.00mm_Horizontal; MPN SM04B-SRSS-TB(LF)(SN); LCSC C160404
J3: TGT_UART; JST_SH_SM04B-SRSS-TB_1x04-1MP_P1.00mm_Horizontal; MPN SM04B-SRSS-TB(LF)(SN); LCSC C160404
J4: SELF_SWD; JST_SH_SM04B-SRSS-TB_1x04-1MP_P1.00mm_Horizontal; MPN SM04B-SRSS-TB(LF)(SN); LCSC C160404
LOGO1: Framework_Logo; Framework-Logo_1.5mm_SilkScreen
R1: 5.1kR; R_0402_1005Metric; MPN 0402WGF5101TCE; LCSC C25905
R2, R3, R5, R12, R13, R14, R15, R16: 22R; R_0402_1005Metric; MPN 0402WGF220JTCE; LCSC C25092
R4, R10, R11: 1kR; R_0402_1005Metric; MPN 0402WGF1001TCE; LCSC C11702
R6, R7, R19: 100kR; R_0402_1005Metric; MPN 0402WGF1003TCE; LCSC C25741
R8, R9, R17, R18: 10kR; R_0402_1005Metric; MPN 0402WGF1002TCE; LCSC C25744
U1: D3V3XA4B10LP-7; Diodes_UDFN-10_1x2.5mm_P0.5mm; MPN D3V3XA4B10LP-7; LCSC C1980462
U2: XC6206P332MR-G; SOT-23; MPN XC6206P332MR-G; LCSC C5446
U3: STM32F072CBT6; LQFP-48_7x7mm_P0.5mm; MPN STM32F072CBT6; LCSC C81720
U4, U5, U6, U7, U8: SN74LVC1T45DBVR; SOT-23-6; MPN SN74LVC1T45DBVR; LCSC C7843

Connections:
/DAP_LED: R10.1, U3.11 (PA1)
/MCU_NRST_DRV: R18.1, U3.18 (PB0), U6.5 (DIR)
/MCU_NRST_IO: U3.19 (PB1), U6.3 (A)
/MCU_SWCLK: U3.26 (PB13), U5.3 (A)
/MCU_SWDIO: U3.27 (PB14), U4.3 (A)
/MCU_SWDIO_DIR: R17.1, U3.25 (PB12), U4.5 (DIR)
/MCU_UART_RX: U3.13 (PA3), U8.3 (A)
/MCU_UART_TX: U3.12 (PA2), U7.3 (A)
/SELF_SWCLK: J4.4, U3.37 (PA14)
/SELF_SWDIO: J4.3, U3.34 (PA13)
/TGT_NRST: J3.1, R14.1
/TGT_SWCLK: J2.3, R13.1
/TGT_SWDIO: J2.2, R12.1
/TGT_UART_RX: J3.3, R15.1
/TGT_UART_TX: J3.2, R16.1, R19.2
/UART_LED: R11.1, U3.14 (PA4)
/USB_DM: R2.1, U3.32 (PA11)
/USB_DM_RAW: J1.A7 (D-), R2.2, U1.2, U1.9 (NC)
/USB_DP: R3.1, U3.33 (PA12)
/USB_DP_RAW: J1.A6 (D+), R3.2, U1.4, U1.7 (NC)
/VBUS: C1.1, C2.1, D1.1 (K), J1.A4 (VBUS), J1.A9 (VBUS), J1.B4 (VBUS), J1.B9 (VBUS), U2.3 (VI)
/VTREF: C7.1, C10.1, C11.1, C12.1, C13.1, C14.1, R5.1, R6.1, R19.1, U4.6 (VCCB), U5.6 (VCCB), U6.6 (VCCB), U7.6 (VCCB), U8.6 (VCCB)
/VTREF_ADC: C8.1, R6.2, R7.1, U3.10 (PA0)
/VTREF_RAW: D3.1 (K), J2.1, R5.2
unnamed: J1.A5 (CC), R1.1
unnamed: R9.2, U3.44 (BOOT0)
unnamed: C9.1, R8.2, U3.7 (NRST)
unnamed: R12.2, U4.4 (B)
unnamed: R13.2, U5.4 (B)
unnamed: R14.2, U6.4 (B)
unnamed: R15.2, U7.4 (B)
unnamed: R16.2, U8.4 (B)

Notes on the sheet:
1. USB-C Host Interface & ESD
2. 3.3V Probe Supply & Target VTref Sense Conditioning
3. STM32F072CBT6 CMSIS-DAPv2 & DMA UART Controller
4. 5x SN74LVC1T45DBVR (1.65V-5.5V) Autoleveling Level Shifters
5. Outward Bezel Target SWD (J2) & UART/nRST (J3) Ports

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
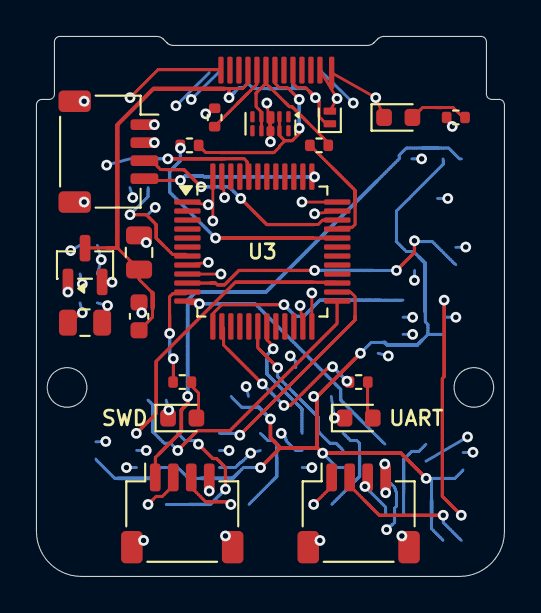
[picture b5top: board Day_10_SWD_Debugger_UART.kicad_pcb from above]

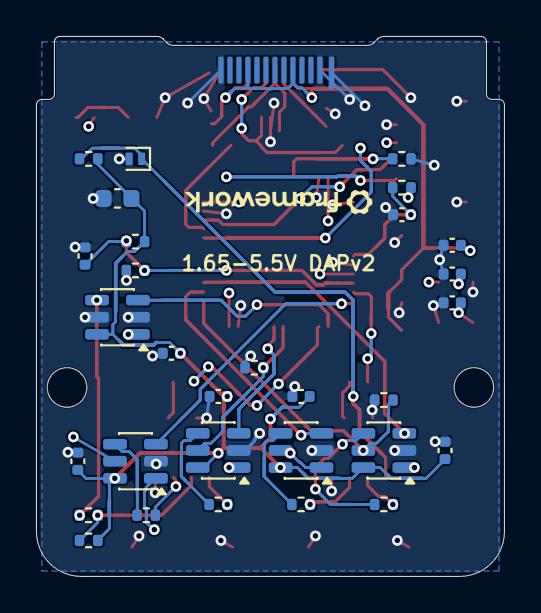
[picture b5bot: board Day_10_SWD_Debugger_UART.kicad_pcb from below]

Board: 4 copper layers, 26.0 x 30.0 mm, 53 parts (31 on the bottom side), 37 nets.
